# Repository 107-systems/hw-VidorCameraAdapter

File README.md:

VidorCameraAdapter
==================

<p align="center">
  
</p>

Adapter to connect a OV2640 camera module to the Mini PCIe connector of the Arduino MKR Vidor 4000.

## Pinout

This adapter uses only the pins of the Mini PCIe connector of the Arduino MKR Vidor (CN1).

| Pin Number  | Pin Name    | Signal | Description                                |
|:-----------:|:-----------:|:------:| ------------------------------------------ |
|  1 | WM.WM_PIO2 PEX_PIN1  | n.c.   | Connected to the WIFI NINA module on Vidor |
|  3 | WM.WM_PIO3 PEX_PIN3  | n.c.   | Connected to the WIFI NINA module on Vidor |
|  5 | WM.WM_PIO4 PEX_PIN5  | n.c.   | Connected to the WIFI NINA module on Vidor |
|  6 | PEX_PIN6             | LED_G  | RGB status LED (green)                     |
|  7 | WM.WM_PIO34 PEX_PIN7 | n.c.   | Connected to the WIFI NINA module on Vidor |
|  8 | PEX_PIN8             | LED_R  | RGB status LED (red)                       |
| 10 | PEX_PIN10            | SDA_V  | I2C to configure OV2640 module             |
| 11 | PEX_PIN11            | n.c.   | Reserved for future use                    |
| 12 | PEX_PIN12            | SCL_V  | I2C to configure OV2640 module             |
| 13 | PEX_PIN13            | DOUT6  | Data from OV2640 module                    |
| 14 | PEX_PIN14            | RST    | reset for OV2640 module                    |
| 16 | PEX_PIN16            | PWDN   | Power down for OV2640 module               |
| 17 | WM.WM_PIO24          | n.c.   | Connected to the WIFI NINA module on Vidor |
| 19 | WM.WM_PIO25          | n.c.   | Connected to the WIFI NINA module on Vidor |
| 20 | PEX_PIN20            | VSYNC  | Sync from OV2640 module                    |
| 22 | PEX_RST              | n.c.   | Pull up resistor on Vidor                  |
| 23 | PEX_PIN23            | PCLK   | Pixel clock from OV2640 module             |
| 25 | PEX_PIN25            | DOUT4  | Data from OV2640 module                    |
| 28 | PEX_PIN28            | HREF   | Sync from OV2640 module                    |
| 30 | PEX_PIN30            | n.c.   | Pull up resistor on Vidor                  |
| 31 | PEX_PIN31            | DOUT5  | Data from OV2640 module                    |
| 32 | PEX_PIN32            | n.c.   | Pull up resistor on Vidor                  |
| 33 | PEX_PIN33            | DOUT7  | Data from OV2640 module                    |
| 42 | PEX_PIN42            | DOUT0  | Data from OV2640 module                    |
| 44 | PEX_PIN44            | DOUT1  | Data from OV2640 module                    |
| 45 | PEX_PIN45            | LED_B  | RGB status LED (blue)                      |
| 46 | PEX_PIN46            | DOUT2  | Data from OV2640 module                    |
| 47 | PEX_PIN47            | XCLK   | Clock for OV2640 module                    |
| 48 | PEX_PIN48            | DOUT3  | Data from OV2640 module                    |
| 49 | PEX_PIN49            | DOUT8  | Data from OV2640 module                    |
| 51 | PEX_PIN51            | DOUT9  | Data from OV2640 module                    |

All GND pins are connected to the GND plane and all +3V3 pins are conntected to the +3V3-rail.

## PCB

### Top

### Bot

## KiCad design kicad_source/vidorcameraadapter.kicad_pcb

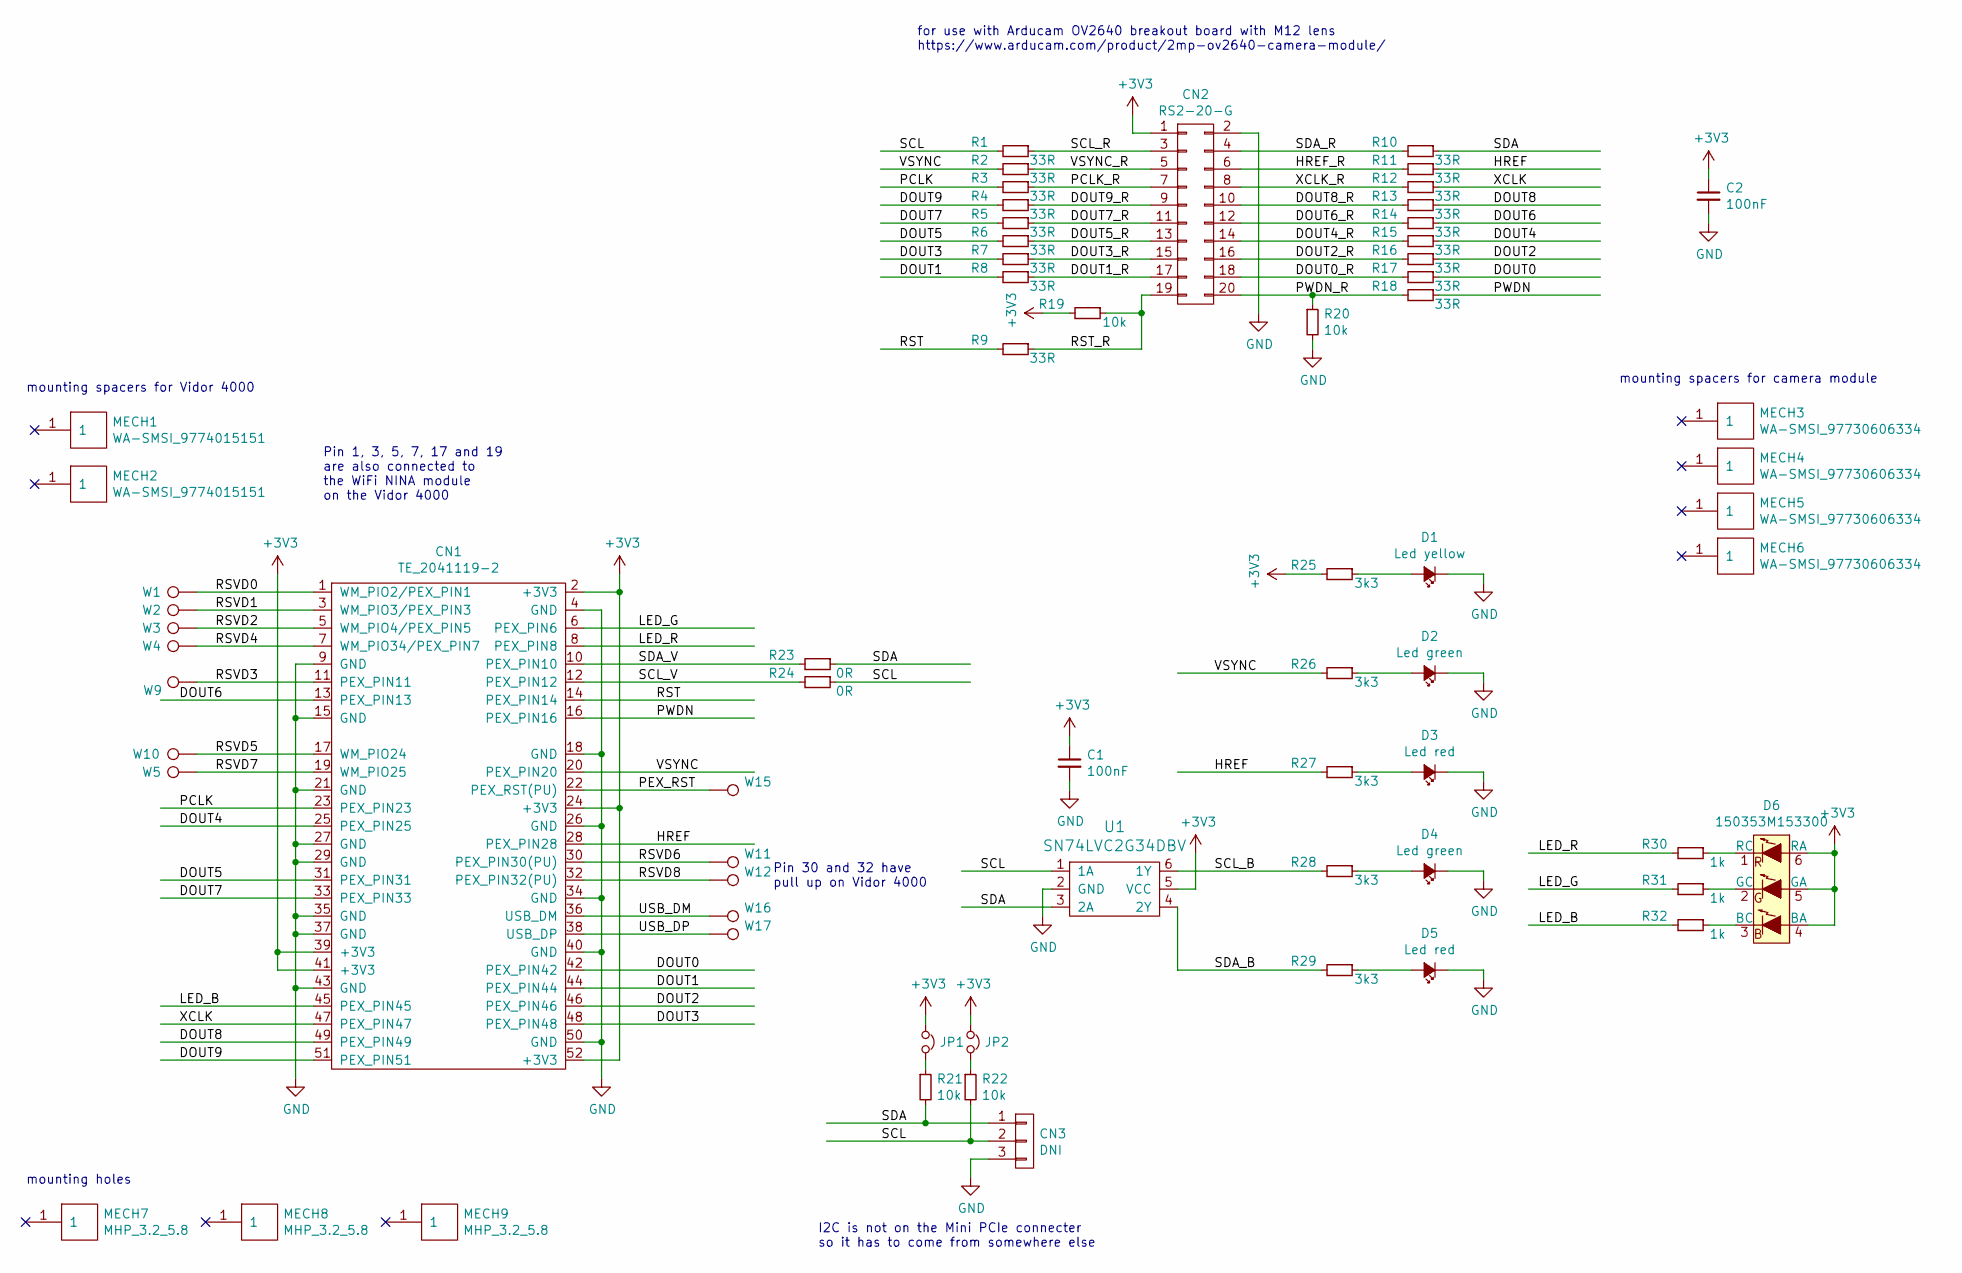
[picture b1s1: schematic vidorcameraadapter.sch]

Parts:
C1, C2: 100nF; C_0603
CN1: TE_2041119-2; MPCIe_4mm
CN2: RS2-20-G; WR-PHD_61302021821
CN3: DNI; Pin_Header_Straight_1x03
D1: Led yellow; LED_0603
D2, D4: Led green; LED_0603
D3, D5: Led red; LED_0603
D6: 150353M153300; LED_RGB_PLLC-6
JP1, JP2: Jumper_NC_Small; SolderJumper_2mm
MECH1, MECH2: WA-SMSI_9774015151
MECH3, MECH4, MECH5, MECH6: WA-SMSI_97730606334
MECH7, MECH8, MECH9: MHP_3.2_5.8
R1, R2, R3, R4, R5, R6, R7, R8, R9, R10, R11, R12, R13, R14, R15, R16, R17, R18: 33R; R_0603
R19, R20, R21, R22: 10k; R_0603
R23, R24: 0R; R_0603
R25, R26, R27, R28, R29: 3k3; R_0603
R30, R31, R32: 1k; R_0603
U1: SN74LVC2G34DBV; SOT-23-6
W1, W2, W3, W4, W5, W9, W10, W11, W12, W15, W16, W17: TEST_1P; SolderWirePad_single_1mmSMD

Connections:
+3V3: C1.1, C2.1, CN1.2 (+3V3), CN1.24 (+3V3), CN1.39 (+3V3), CN1.41 (+3V3), CN1.52 (+3V3), CN2.1, D6.4 (BA), D6.5 (GA), D6.6 (RA), JP1.1, JP2.1, R19.2, R25.2, U1.5 (VCC)
/DOUT0: CN1.42 (PEX_PIN42), R17.1
/DOUT0_R: CN2.18, R17.2
/DOUT1: CN1.44 (PEX_PIN44), R8.2
/DOUT1_R: CN2.17, R8.1
/DOUT2: CN1.46 (PEX_PIN46), R16.1
/DOUT2_R: CN2.16, R16.2
/DOUT3: CN1.48 (PEX_PIN48), R7.2
/DOUT3_R: CN2.15, R7.1
/DOUT4: CN1.25 (PEX_PIN25), R15.1
/DOUT4_R: CN2.14, R15.2
/DOUT5: CN1.31 (PEX_PIN31), R6.2
/DOUT5_R: CN2.13, R6.1
/DOUT6: CN1.13 (PEX_PIN13), R14.1
/DOUT6_R: CN2.12, R14.2
/DOUT7: CN1.33 (PEX_PIN33), R5.2
/DOUT7_R: CN2.11, R5.1
/DOUT8: CN1.49 (PEX_PIN49), R13.1
/DOUT8_R: CN2.10, R13.2
/DOUT9: CN1.51 (PEX_PIN51), R4.2
/DOUT9_R: CN2.9, R4.1
/HREF: CN1.28 (PEX_PIN28), R11.1, R27.2
/HREF_R: CN2.6, R11.2
/LED_B: CN1.45 (PEX_PIN45), R32.2
/LED_G: CN1.6 (PEX_PIN6), R31.2
/LED_R: CN1.8 (PEX_PIN8), R30.2
/PCLK: CN1.23 (PEX_PIN23), R3.2
/PCLK_R: CN2.7, R3.1
/PEX_RST: CN1.22 (PEX_RST(PU)), W15.1
/PWDN: CN1.16 (PEX_PIN16), R18.1
/PWDN_R: CN2.20, R18.2, R20.1
/RST: CN1.14 (PEX_PIN14), R9.2
/RST_R: CN2.19, R9.1, R19.1
/RSVD0: CN1.1 (WM_PIO2/PEX_PIN1), W1.1
/RSVD1: CN1.3 (WM_PIO3/PEX_PIN3), W2.1
/RSVD2: CN1.5 (WM_PIO4/PEX_PIN5), W3.1
/RSVD3: CN1.11 (PEX_PIN11), W9.1
/RSVD4: CN1.7 (WM_PIO34/PEX_PIN7), W4.1
/RSVD5: CN1.17 (WM_PIO24), W10.1
/RSVD6: CN1.30 (PEX_PIN30(PU)), W11.1
/RSVD7: CN1.19 (WM_PIO25), W5.1
/RSVD8: CN1.32 (PEX_PIN32(PU)), W12.1
/SCL: CN3.2, R1.2, R22.2, R24.1, U1.1 (1A)
/SCL_B: R28.2, U1.6 (1Y)
/SCL_R: CN2.3, R1.1
/SCL_V: CN1.12 (PEX_PIN12), R24.2
/SDA: CN3.1, R10.1, R21.2, R23.1, U1.3 (2A)
/SDA_B: R29.2, U1.4 (2Y)
/SDA_R: CN2.4, R10.2
/SDA_V: CN1.10 (PEX_PIN10), R23.2
/USB_DM: CN1.36 (USB_DM), W16.1
/USB_DP: CN1.38 (USB_DP), W17.1
/VSYNC: CN1.20 (PEX_PIN20), R2.2, R26.2
/VSYNC_R: CN2.5, R2.1
/XCLK: CN1.47 (PEX_PIN47), R12.1
/XCLK_R: CN2.8, R12.2
GND: C1.2, C2.2, CN1.4 (GND), CN1.9 (GND), CN1.15 (GND), CN1.18 (GND), CN1.21 (GND), CN1.26 (GND), CN1.27 (GND), CN1.29 (GND), CN1.34 (GND), CN1.35 (GND), CN1.37 (GND), CN1.40 (GND), CN1.43 (GND), CN1.50 (GND), CN2.2, CN3.3, D1.1 (K), D2.1 (K), D3.1 (K), D4.1 (K), D5.1 (K), R20.2, U1.2 (GND)
unnamed: D1.2 (A), R25.1
unnamed: D2.2 (A), R26.1
unnamed: D3.2 (A), R27.1
unnamed: D4.2 (A), R28.1
unnamed: D5.2 (A), R29.1
unnamed: D6.1 (RC), R30.1
unnamed: D6.2 (GC), R31.1
unnamed: D6.3 (BC), R32.1
unnamed: JP1.2, R21.1
unnamed: JP2.2, R22.1

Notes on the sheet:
Pin 30 and 32 have pull up on Vidor 4000
mounting spacers for Vidor 4000
mounting spacers for camera module
I2C is not on the Mini PCIe connecter so it has to come from somewhere else
for use with Arducam OV2640 breakout board with M12 lens https://www.arducam.com/product/2mp-ov2640-camera-module/
mounting holes
Pin 1, 3, 5, 7, 17 and 19 are also connected to the WiFi NINA module on the Vidor 4000

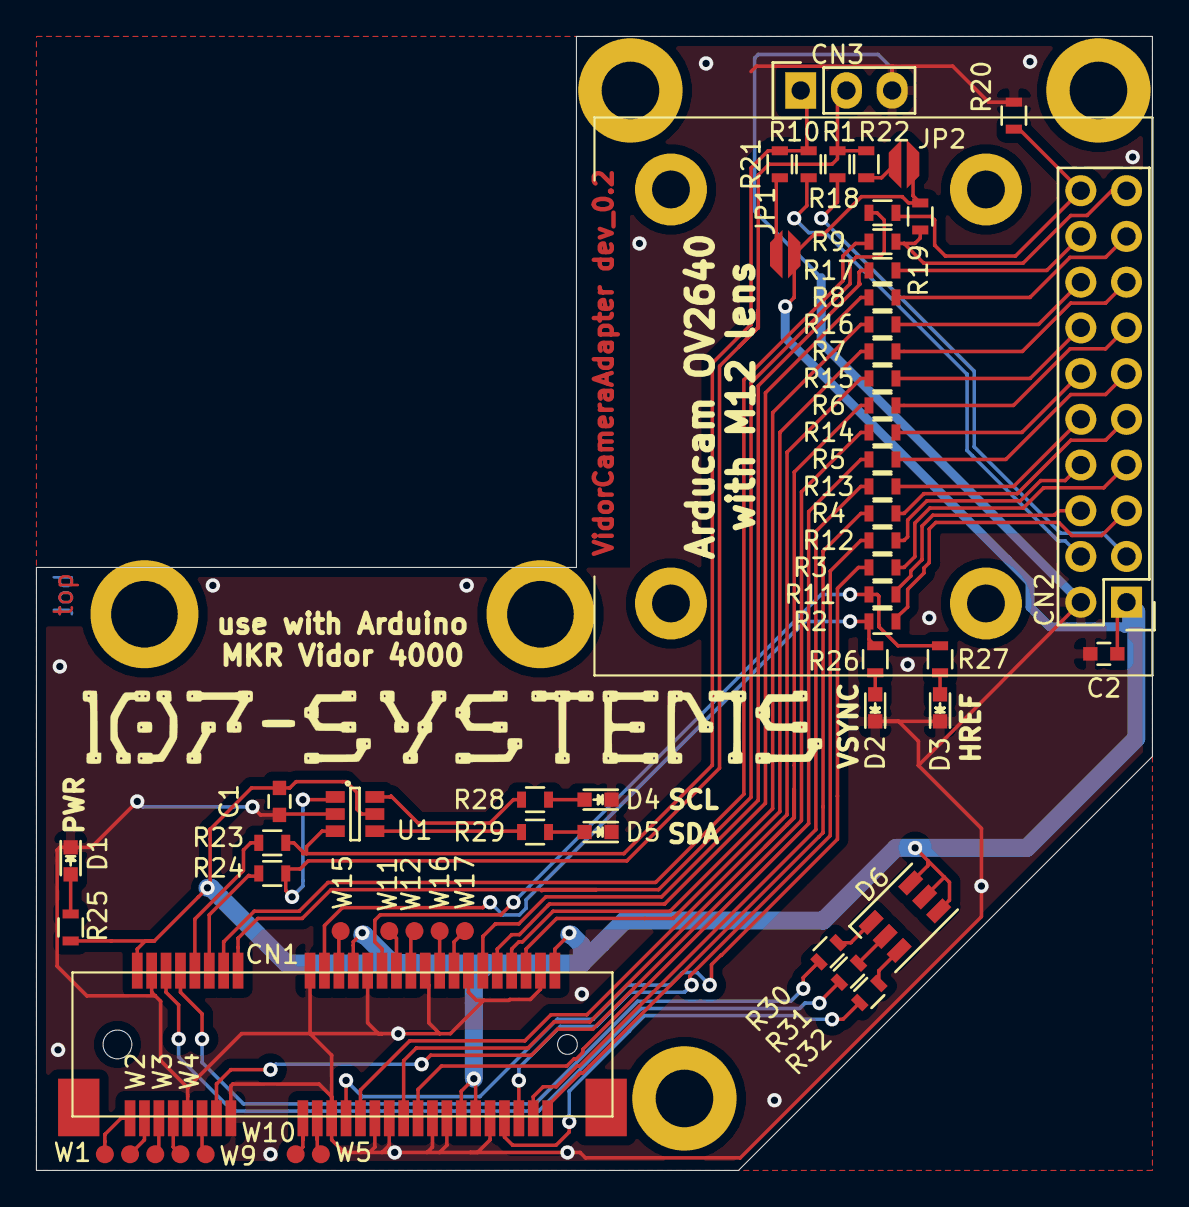
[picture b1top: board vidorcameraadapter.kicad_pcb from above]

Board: 2 copper layers, 62.0 x 63.0 mm, 67 parts (0 on the bottom side), 67 nets.

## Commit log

2020-01-28 added kicad source
2020-01-28 updated readme, added images
2020-01-28 added schematic pdf
2020-01-28 corrected spacers, added resistors, made layout
2020-01-28 added 3d models, added mounting holes
2020-01-28 added testpoints for all unused pins
2020-01-29 updated layout, made edge smoother, generated pdf schematic and images
2020-01-30 added pull up for I2C and RST, added pull down for pwdn
2020-01-30 connected I2C to Vidor 4000, added LEDs
2020-01-31 added RGB led
2020-01-31 placed all new parts in layout
2020-01-31 moved camera connector to unblock HDMI connector on Vidor 4000, connected all traces again
2020-01-31 updated images
2020-02-01 added logo and description on silkscreen
2020-02-03 added jumper for I2C pullup, added buffer ic for I2C leds, made mounting holes as parts, made DRC, updated images
2020-02-05 moved pins on the Vidor connector to free NINA pins and pins with pull up, exchanged PCLK and XCLK, added pdfs and generated images
2020-02-05 changed pinning to fit to https://github.com/107-systems/viper-vidor-fpga
2020-02-08 added pinout description to readme
2020-02-22 changed resistors for led from 1k to 3k3, added changes file
2020-02-22 added step file of pcb
2020-02-23 updated symbold for vidor mpcie connector in schematic
2020-02-23 made pcb smaller to avoid collision with MKR connector
2020-02-24 Centering contents of pin-out table
2020-03-16 Adding picture of populated PCBs with camera module
2020-04-19 added test software to toggle all LEDs on the board
2020-04-19 restored design files from master
2020-04-21 added timeout for Serial init, replaced defines by consts
2020-04-22 Check for correct sketch structure during CI build
2020-04-22 Use Travis CI for compilation testing of sketches
    All sketches under the src folder will be compiled for MKR Vidor 4000 on every pull request and push.
2020-04-22 Check for commonly misspelled words during CI build
    Use codespell to check the repository's files for typos.
    In the event of false positives, words to ignore may be added to etc/codespell-ignore-words-list.txt. Although the typo check is case-insensitive, the ignore words list is case-sensitive, and the mis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
2020-04-22 Use TravisBuddy to comment on PRs that result in a failed CI build
    The automatic comment from TravisBuddy will notify the PR author of the failed build and prompt them to resolve the issue.
2020-04-22 Check files for consistent formatting during CI build
    All non-generated files must:
    - Not start with a blank line
    - Not contain true tabs
    - Not contain trailing whitespace
    - Use Unix-style line endings
    - Not contain extra blank lines at the end of the file
2020-07-09 Add logo for project viper
2020-11-30 Link to viper logo in .github default repository.
2020-11-30 Removing viper logo file since it was moved into the shared repository
2020-12-01 Update viper logo path.
2020-12-04 Add a CI workflow to sync organization-wide labels
    The workflow will configure the labels of this repository according to the universal labels defined by https://github.com/107-systems/.github/blob/main/universal-repository-labels.json combined with 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
2020-12-30 Update viper firmware link.
